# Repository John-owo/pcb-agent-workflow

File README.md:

# pcb-agent-workflow

**繁體中文** | [English](README.en.md)

用 Claude Code 或 Codex 當助手，在 KiCad 10 設計 PCB、交 JLCPCB 製造的一套工作流程。

這套流程來自一塊 4 層 GNSS 測試板（u-blox MAX-M10S，25 × 36.5 mm）從設計、審查、報價、送審、客服往返到確認生產稿的實際經驗。重複有用的做法寫成文件和 skill；踩過的雷寫成檢查項目。

**第一次做 PCB？** 從 [新手入門](docs/getting-started.md) 開始：從安裝 KiCad 走到在 JLC 下單，每一步寫你要做什麼、可以請 agent 做什麼、怎麼確認做對了。其他文件之後再看。

## 內容

| 路徑 | 內容 |
|---|---|
| [docs/getting-started.md](docs/getting-started.md) | **新手入門**：第一塊板的範圍、環境、原理圖、選料、板子規則、佈線、匯出、下單 |
| [docs/first-board-checklist.md](docs/first-board-checklist.md) | 送廠前的檢查清單，給人看，也給 agent 審查用 |
| [docs/glossary.md](docs/glossary.md) | 術語表：Gerber、BOM、CPL、DFM、工藝邊、Basic／Extended 料等 |
| [docs/workflow/collaboration.md](docs/workflow/collaboration.md) | 人與多個 agent 協作：單一寫入者、WORKLOG、接手順序、審查最多兩輪、哪些動作要使用者同意 |
| [docs/workflow/kicad-tools.md](docs/workflow/kicad-tools.md) | KiCad 原生 CLI 與 KiCad MCP 的分工、常用命令、修改 PCB 前的保全 |
| [docs/workflow/release-package.md](docs/workflow/release-package.md) | 固定發行包：內容、雜湊清單、release-checks、版本資料夾命名 |
| [docs/workflow/jlc-ordering.md](docs/workflow/jlc-ordering.md) | JLC 下單：服務等級、BOM／CPL、配料核對、壓成本、送單設定、付款後流程 |
| [skills/jlc-support/](skills/jlc-support/SKILL.md) | 跟 JLC 客服、工程、業務窗口溝通的 skill：寫信結構、六種範本、期限計算腳本、工具搭配、停止條件 |
| [skills/jlc-production-review/](skills/jlc-production-review/SKILL.md) | 審查工廠生產稿與貼裝確認的 skill：把工廠 CAM 稿對齊回原始 Gerber 逐層比對、分類差異、核對貼裝；附比對腳本與 BOM／CPL 檢查 |
| [skills/readable-schematic-layout/](skills/readable-schematic-layout/SKILL.md) | 把原理圖與佈局畫成人類好讀、好除錯的 skill：內建 symbol、電源 symbol、實際畫線、依流向分區、文字不重疊；附 netlist 比對與腳號對焊盤檢查腳本，證明只改畫法、沒改電路 |
| [skills/kicad-enclosure-step/](skills/kicad-enclosure-step/SKILL.md) | 把 KiCad 板子匯出成含全部零件的 STEP，給外殼設計用：盤點缺模型的零件、找原廠模型或依規格書自畫、對齊、用暫存副本匯出（不改板檔），逐顆自動檢查位置，最後寫外殼注意事項 |
| [.claude-plugin/marketplace.json](.claude-plugin/marketplace.json) | Claude Code 與 Codex 共用的 plugin marketplace：每個 skill 一個 plugin，加上選用的寄信確認 hook |
| [plugins/jlc-send-guard/](plugins/jlc-send-guard/) | 選用的 Claude Code hook：Gmail 寄出類工具執行前強制確認 |
| [templates/](templates/) | 新專案用的 `AGENTS.md`、`CLAUDE.md`、`WORKLOG.md`、`README.md`，以及 KiCad 專案的 `.gitignore` |
| [scripts/](scripts/) | 發行包打包驗證、Konnect stdio 呼叫器、本 repo 的隱私掃描與 skill 檢查（各 skill 專用的腳本放在 skill 自己的 `scripts/`） |
| [examples/max-m10s-breakout-revc/](examples/max-m10s-breakout-revc/README.md) | 實際下單過的範例設計包：KiCad 原生檔、Gerber、BOM、CPL、裝配圖、驗證紀錄 |
| [examples/max-m10s-breakout-revc-cad/](examples/max-m10s-breakout-revc-cad/README.md) | 上面那塊板的外殼設計用 STEP（含全部零件）、預覽圖與匯出設定；kicad-enclosure-step 的範例 |

## 流程總覽

```mermaid
flowchart LR
  A[設計<br/>KiCad 10] --> B[驗證<br/>ERC / DRC / agent 審查]
  B --> C[固定發行包<br/>雜湊清單]
  C --> D[上傳與送審<br/>配料核對]
  D --> E[付款]
  E --> F[生產稿比對]
  F --> G[使用者確認]
  G --> H[到貨與實測]
  S([jlc-support<br/>客服與工程溝通]) -.-> D
  S -.-> E
  S -.-> F
  R([jlc-production-review<br/>生產稿與貼裝審查]) -.-> F
```

## 開始使用

### 新專案

把 `templates/` 裡的四個 Markdown 檔複製到 PCB 專案根目錄，把 `<...>` 換成自己的內容；`kicad-project.gitignore` 複製後改名為 `.gitignore`。專案已經有 `README.md` 的話，不要直接覆蓋，把範本的段落合併進去。之後每次接手，agent 會從 `README.md` 和 `WORKLOG.md` 讀起。

### 安裝 skill

四個 skill 各是一個 plugin，可以只裝需要的。Claude Code 與 Codex 讀同一份 marketplace（`.claude-plugin/marketplace.json`）和同一份 `SKILL.md`。

| plugin | 用途 |
|---|---|
| `jlc-support` | 跟 JLC 客服、工程、業務窗口溝通；附確認稿期限計算 |
| `jlc-production-review` | 審查生產稿與貼裝確認；附 CAM 比對與 BOM／CPL 檢查腳本 |
| `readable-schematic-layout` | 原理圖與佈局畫成好讀、好除錯的樣子；附 netlist 與腳號對焊盤檢查 |
| `kicad-enclosure-step` | 把板子匯出成含全部零件的 STEP 給外殼設計；附盤點、匯出、逐顆位置檢查與自畫模型腳本 |
| `jlc-send-guard` | 選用的 Claude Code hook，見下方「寄信確認 hook」；預設停用 |

**Claude Code**（在對話裡輸入）：

```text
/plugin marketplace add John-owo/pcb-agent-workflow
/plugin install jlc-support@pcb-agent-workflow
```

Claude Code 2.1.275 以後也可以一步完成：`/plugin install jlc-support --marketplace John-owo/pcb-agent-workflow`。更新用 `/plugin marketplace update pcb-agent-workflow`。

**Codex**（在終端機）：

```bash
codex plugin marketplace add John-owo/pcb-agent-workflow
```

```bash
codex plugin add jlc-support@pcb-agent-workflow
```

更新用 `codex plugin marketplace upgrade`。把 `jlc-support` 換成表中其他名稱，就能裝其他 plugin。裝好後重新開一個對話，跟 agent 說「幫我寫信催 JLC 的 DFM」「幫我比對工廠寄來的生產稿」「把原理圖改成好讀的畫法，不要改電路」「我要設計外殼，給我含全部零件的 STEP」，就會套用對應的 skill。

**腳本的相依套件**：`jlc-production-review` 的 CAM 比對腳本需要 Python 3.12 與固定版本的套件，在 skill 資料夾裡執行 `python -m pip install -r scripts/requirements-cam.txt`（建議裝在 venv）。`kicad-enclosure-step` 需要 KiCad 10；它的 `step_report.py`、`simple_model.py`、`verify_placement.py` 另需 [CadQuery](https://github.com/CadQuery/cadquery)（`python -m pip install cadquery`，建議裝在 venv），範例與重現指令見 [examples/max-m10s-breakout-revc-cad](examples/max-m10s-breakout-revc-cad/README.md)。其他腳本只用 Python 標準庫。

#### 手動安裝（不用 plugin）

複製 skill 資料夾到 agent 的 skills 目錄。先建立目錄再複製；沒有這個目錄時，複製指令會把 skill 的內容直接攤在 `skills/` 底下，agent 就找不到它。

```bash
git clone https://github.com/John-owo/pcb-agent-workflow.git
```

Claude Code（macOS／Linux／Git Bash）：

```bash
mkdir -p ~/.claude/skills && cp -r pcb-agent-workflow/skills/jlc-support ~/.claude/skills/
```

Codex（Codex 文件寫的使用者 skill 目錄是 `~/.agents/skills`；舊的 `~/.codex/skills` 未驗證）：

```bash
mkdir -p ~/.agents/skills && cp -r pcb-agent-workflow/skills/jlc-support ~/.agents/skills/
```

Windows PowerShell（Codex 的話把 `.claude` 換成 `.agents`）：

```powershell
New-Item -ItemType Directory -Force "$HOME\.claude\skills" | Out-Null
Copy-Item -Recurse -Force pcb-agent-workflow\skills\jlc-support "$HOME\.claude\skills\"
```

裝好後 `~/.claude/skills/jlc-support/SKILL.md`（或 `~/.agents/skills/` 底下的同一路徑）要存在。更新時重跑同一組指令。只想在單一專案使用，就放到該專案的 `.claude/skills/` 或 `.agents/skills/`。手動安裝不含 `jlc-send-guard` hook。

#### 寄信確認 hook（選用，只限 Claude Code）

`jlc-send-guard` 在 Gmail connector 的寄出類工具（名稱含 `send`、`reply`、`forward`）執行前，強制跳出確認，auto mode 也一樣。草稿工具不受影響。它預設停用，要用時自己啟用：

```text
/plugin install jlc-send-guard@pcb-agent-workflow
/plugin enable jlc-send-guard@pcb-agent-workflow
```

限制：

- 它用正規表示式比對工具名稱：`^mcp__.*[Gg][Mm][Aa][Ii][Ll].*__.*([Ss]end|[Rr]eply|[Ff]orward)`。connector 改名後可能漏攔，請在 `/mcp` 看你的 Gmail 工具名稱有沒有被涵蓋；名稱相近的其他工具可能被多攔，多攔只會多一次確認。
- **擋不住瀏覽器上的動作。** hook 看不到頁面網址和按鈕文字，所以 Claude in Chrome 點 Confirm、Submit 不在它的範圍內；那部分只靠 skill 的硬規則和 Chrome 擴充的網站權限。
- Codex 端沒有驗證過。Codex 的 plugin hook 要先經使用者信任才會執行，ChatGPT 的 Gmail connector 能不能被攔也不確定。
- 它是多一道防線，不取代 skill 的硬規則：寄出前仍要使用者在對話中明確同意。

### 搭配的 KiCad 分析 skill

原理圖分析、BOM、DRC 審查、EMC、SPICE 等 skill 使用 [aklofas/kicad-happy](https://github.com/aklofas/kicad-happy)（MIT）。本 repo 不附副本，請依該 repo 的說明安裝。這套流程實際用到的有 `kicad`、`bom`、`jlcpcb`、`lcsc`、`datasheets`、`emc`、`spice`。

### docs/agents 是什麼

`docs/agents/` 是給 [mattpocock/skills](https://github.com/mattpocock/skills) 那套工程類 skill（`triage`、`to-tickets`、`to-spec` 等）讀的設定：issue 記在哪裡、triage 標籤叫什麼。沒安裝那套 skill 就用不到，可以忽略。

### Codex 與 Claude Code 交接

兩個 agent 輪流接手同一個任務時，交接格式見 [John-owo/codex-cc-handoff](https://github.com/John-owo/codex-cc-handoff)。

## 核心原則

- **一個工作目錄同時只有一位寫入者。** 換手時在 WORKLOG 記錄 owner 與停止點。
- **改 PCB 前先保全完整備份。** 雜湊清單只能識別檔案，不能還原。
- **ERC／DRC 通過，不等於電氣正確、板廠接受或實板能動。**
- **付款、送單、寄信、確認生產稿，每一次都等使用者同意。** agent 做到起草和準備為止。唯一的例外是催辦與純技術澄清：使用者可以說明範圍和期限，事先授權。
- **固定發行包與動態進度分開。** 交給工廠的版本不再改；訂單進度另外記。

## 限制

- 範例板完成了 ERC／DRC 與 agent 審查，並由 JLCPCB 製造與 SMT 組裝。兩片組裝板已完成實測：上電、UART、被動天線 3D 定位、PPS 1 Hz 與 I2C 皆通過；回灌 A-GNSS 輔助資料後，定位時間約縮短為冷啟動的 1/8。範例是送單時的發行包；工廠 CAM 之後做的微調不在裡面。實測程序與結果見 [examples/max-m10s-breakout-revc-tests](examples/max-m10s-breakout-revc-tests/README.md)。
- JLC 的期限、價格、料庫狀態是 2026-09 的觀察，以當下的網站和信件為準。
- 流程以 Windows、KiCad 10、JLCPCB 為主要環境。其他板廠可以參考溝通原則，但網站流程不同。

## 支援範圍

這套流程只在下面的環境驗證過：

| 項目 | 支援 |
|---|---|
| 作業系統 | Windows |
| EDA | KiCad 10 |
| agent | Claude Code、Codex（兩者都要能用）。plugin 安裝在 Claude Code 2.1.299、Codex CLI 0.163 測過 |
| 板廠 | JLCPCB |
| 收貨地 | 台灣（順豐） |

SKILL.md 與腳本是兩個 agent 共用的基準。只有 Claude Code 驗證過的加強功能另外標明：目前只有 `jlc-send-guard` hook。拿掉它，skill 一樣完整，硬規則照樣適用。

其他環境（macOS、Linux、其他 KiCad 版本、PCBWay 等其他板廠）可能可以用，但沒有驗證。這類 issue 會標成 `wontfix`，回覆「可能可用，未驗證」；溝通原則不受板廠限制，可以照用。

## 授權

MIT，見 [LICENSE](LICENSE)。範例中改自 KiCad 官方元件庫的 footprint 與 symbol，以及其他第三方內容的來源，見 [NOTICE](NOTICE)。原廠 datasheet 不隨附，範例 README 列有原廠連結。

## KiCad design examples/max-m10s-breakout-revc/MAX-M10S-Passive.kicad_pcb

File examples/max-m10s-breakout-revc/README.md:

# MAX-M10S 被動天線 GNSS 轉接板（Rev C，OSP，僅頂面組裝）

以 u-blox MAX-M10S 為核心的小型 GNSS 轉接板，接被動式天線，供麵包板或主控板以 UART／I2C 使用。原生設計為 KiCad 10，發行日期 2026-09-21。

## 板子規格

- 尺寸 25.0 × 36.5 mm，4 層，板厚 1.6 mm，表面處理 OSP，疊構按 JLC04161H-7628 設定。
- U1：MAX-M10S-00B，使用預設低增益內建 LNA。
- J1：I-PEX MHF I（20279-001E-03）接被動式 50 Ω 天線，不供天線電源。D1 為天線端 ESD 保護。
- J2、J3：兩支 1×6、2.54 mm 排針，從板底插入，兩排間距 17.78 mm。
- TX／RX／PPS 串 33 Ω，I2C 有 4.7 kΩ 上拉，電源 LED，PPS LED 經 BSS138 緩衝。另有 5 個測試焊盤（TP1、TP2、TP4–TP6）。
- 無 RTC 備援電源：U1 pin 6（V_BCKP）刻意不接，板上沒有電池或超級電容。
- 原理圖註記：UART 9600 8N1，I2C 位址 0x42。

## 接線

- 只接外部穩壓 3.3 V 電源與 3.3 V 邏輯，不耐 5 V。
- 模組 TX → 主控 RX，模組 RX → 主控 TX，並共地。
- 排針由天線端往下：
  - J2：3V3 / GND / TX / RX / PPS / EXTINT
  - J3：GND / SCL / SDA / RESET_N / SAFEBOOT_N / GND
- 沒有備援電源，完全斷電後需由主控重新設定 GNSS。
- 移除 GNSS 電源前先斷開主控訊號。
- PPS LED 閃爍不代表已定位。

## 檔案

| 路徑 | 內容 |
|---|---|
| `MAX-M10S-Passive.kicad_pro` / `.kicad_sch` / `.kicad_pcb` / `.kicad_dru` | KiCad 10 原生專案、原理圖、PCB、自訂設計規則 |
| `fp-lib-table`、`sym-lib-table` | 專案元件庫表，以 `${KIPRJMOD}` 相對路徑指向下兩項 |
| `footprints/PassiveGNSS.pretty/` | 專案 footprint 庫 |
| `symbols/PassiveGNSS.kicad_sym` | 專案 symbol 庫 |
| `design.json` | 元件、網路、料號與 PCB 座標的機器可讀摘要（KiCad 不讀此檔） |
| `manufacturing/gerbers-board.zip` | 單板 Gerber、鑽孔檔與 Gerber job 檔 |
| `manufacturing/BOM-JLCPCB-top-only.csv` | 板廠組裝 BOM：11 組料、每片 17 個元件，含 LCSC 料號 |
| `manufacturing/CPL-board-top-only.csv` | 板廠貼片座標，僅 Top，單板座標 |
| `manufacturing/assembly-orientation.pdf` / `.csv` / `-1.png` | 裝配方向圖與對照表（pin 1、極性端、座標） |
| `manufacturing/BOM-customer-headers.csv` | 自行焊接的排針 J2、J3 |
| `manufacturing/schematic.pdf` | 原理圖 PDF |
| `verification/erc.json`、`drc.json` | 發行時的原生 ERC／DRC 結果 |
| `verification/release-checks.json` | 發行差異核對摘要 |
| `verification/independent-release-review.md` | 獨立審查紀錄（範圍見下文） |

`PassiveGNSS` 庫裡還有 Rev C 板上沒用到的項目：footprint `ADCM_S05R5SA`、`CPH3225A`（已移除的備援電源）、`Fiducial_1mm`、`ToolingHole_2mm`，symbol `BAS116`、`C_Polarized`、`D`。部分 footprint／symbol 衍生自 KiCad 官方元件庫，來源與授權見 repo 的 NOTICE。

## 製造用哪些檔

以下四項是同一套，一起使用，不要和其他版本的檔案混用：

1. `manufacturing/gerbers-board.zip`：製板
2. `manufacturing/BOM-JLCPCB-top-only.csv`：組裝 BOM
3. `manufacturing/CPL-board-top-only.csv`：貼片座標
4. `manufacturing/assembly-orientation.pdf`（另有 `.csv`、`.png`）：裝配方向，用來核對板廠的貼片預覽

補充：

- Gerber 是單板，不含拼板工藝邊和定位點。原發行時的安排是由板廠加工藝邊與定位點、交貨前拆邊；這項服務與做法須由板廠確認。
- 工廠只組裝頂面 17 個元件。J2、J3 排針不在組裝 BOM／CPL 內，依 `BOM-customer-headers.csv` 自行從板底插入焊接（每片 2 支）。原生設計仍保留 J2、J3，作為成品的一部分。
- OSP 板收到後盡早焊排針。

## 已驗證

- **原生 ERC／DRC**（KiCad 10.0.6，發行時 2026-09-21）：ERC 0 項違規；DRC 0 項違規、0 個未連線項目、0 個原理圖／PCB 一致性問題。報告含 error、warning、exclusion 三種等級，見 `verification/`。
- **本副本重跑**（2026-10-02，KiCad 10.0.6 `kicad-cli`，`--severity-all`，DRC 加 `--schematic-parity`）：結果相同。元件庫經 `${KIPRJMOD}` 正常載入，沒有缺 symbol 或 footprint 的警告。這次重跑的輸出沒有放進套件，以免改動發行時的 `verification/`；可以用 [kicad-tools.md](../../docs/workflow/kicad-tools.md) 第 5 節的命令自行重現。
- **發行差異核對**（`release-checks.json`）：與前一版 Rev C 相比，PCB 幾何、走線、焊盤與網路不變。這一版只改了 D1 料號文字、資料表連結、OSP 製造屬性與組裝清單。Gerber ZIP 與當時上傳板廠的檔案逐位元相同。
- **獨立審查**（`independent-release-review.md`）：由唯讀的審查 agent 檢查發行檔案（README、BOM、CPL、裝配表、ERC／DRC 報告等）彼此是否一致，沒有發現致命的不一致或遺漏。審查範圍只到這些檔案的一致性；審查的是原始發行版的 README，本 README 為公開範例重寫，不在審查範圍內。審查者沒有重新開啟或重算 Gerber ZIP，也沒有核對網站狀態、疊構實作、PDF 呈現、電氣／RF／EMC／DFM 行為或實板。

## 未驗證

- ERC／DRC 通過，不代表電路正確、板廠會接受，或實板能正常工作。
- EMC：先前的設計審查只做過 EMC 啟發式分析，留下未經實測的風險提示，例如介面訊號換層處 1 mm 內沒有獨立的 GND stitching via。這些不算通過 EMC，也沒有做過 EMC 測試。
- SPICE：自動模擬因本機模擬器逾時而跳過，沒有 SPICE 通過的結果。
- 這一版只核對交付差異，不是重新做的完整電氣／EMC 驗證。
- 板廠 DFM 審核與貼片確認的結果不在本套件內。板廠的最終生產稿與元件方向須另行確認。
- 兩片組裝板已通過實測程序第 3–7 步；M10S 輔助定位只在實板試過一次回灌（MGA-DBD＋位置）。實測程序與結果見 [max-m10s-breakout-revc-tests](../max-m10s-breakout-revc-tests/README.md)。先前在 NEO-6M 上做的 ALP／AOP 測試，不能當作 M10S 的結果。

## 已知注意事項

- **D1 footprint 名稱與實際料號不同**：footprint 名稱是 `PassiveGNSS:PESD3V3C1BSF`，實際料號是 Nexperia PESD3V3Z1BSFYL（LCSC C2908830）。兩者用同一組焊盤（DSN0603-2／SOD962-2，0.4 mm pitch），footprint 名稱沒改。採購以 BOM 的料號為準。
- **D1 焊盤間距**：依 Nexperia 建議焊盤，兩焊盤實際間距約 0.144 mm，小於專案預設間距（網路類別 0.2 mm）。`.kicad_dru` 對 D1 焊盤之間（0.13 mm）以及 RF 走線到 D1 焊盤（0.15 mm）設了局部規則，另規定 RF 與 GND 鋪銅保持 1.0 mm。
- **Gerber job 檔的表面處理欄位**：`gerbers-board.zip` 內 `MAX-M10S-Passive-job.gbrjob` 的 `Finish` 寫的是 `ENIG`，而 PCB 設定與本版製造規格都是 OSP。Gerber 沒有在改成 OSP 後重新產生，所以下單時要在訂單上選 OSP。
- **J1 座標**：CPL 用的是連接器的機構中心 (15.800, 33.700)，和 RF 接點焊盤 (15.800, 32.175) 位置不同。須確認外殼和中心接點的方向。
- **極性**：元件頂面的標記不一定代表極性。D2、D3、Q1、U1 都要依 `assembly-orientation.pdf` 的 pin 1 和極性端，比對板廠的貼片預覽。
- **design.json 的元件數**：備註寫 19 個元件，這個數字包含自行焊接的 J2、J3；板廠組裝是 17 個。
- 設計時曾和 SparkFun 公開的 MAX-M10S breakout 原理圖逐項比較差異與取捨。本設計的電路與檔案是重新繪製的，沒有複製 SparkFun 的檔案。
- U1 與 J1 的 footprint 依原廠資料建立：MAX-M10S Integration Manual UBX-20053088 R05（焊盤、鋼網開口），I-PEX 20279 圖面 rev.29。這些原廠資料沒有附在本套件內。

## 原廠資料表

原廠資料表、整合手冊和圖面有著作權，不附在本套件內，請到原廠網站下載。下表取自原理圖 symbol 的 Datasheet 欄位：

| 位號 | 料號 | 廠商 | 資料表 |
|---|---|---|---|
| U1 | MAX-M10S-00B | u-blox | https://content.u-blox.com/sites/default/files/MAX-M10S_DataSheet_UBX-20035208.pdf |
| D1 | PESD3V3Z1BSFYL | Nexperia | https://assets.nexperia.com/documents/data-sheet/PESD3V3Z1BSF.pdf |
| Q1 | BSS138 | onsemi | https://www.onsemi.com/pdf/datasheet/bss138-d.pdf |

其他元件（電阻、電容、LED、J1、排針）的 Datasheet 欄位是空的，可依 BOM 上的製造商料號到原廠網站查詢。

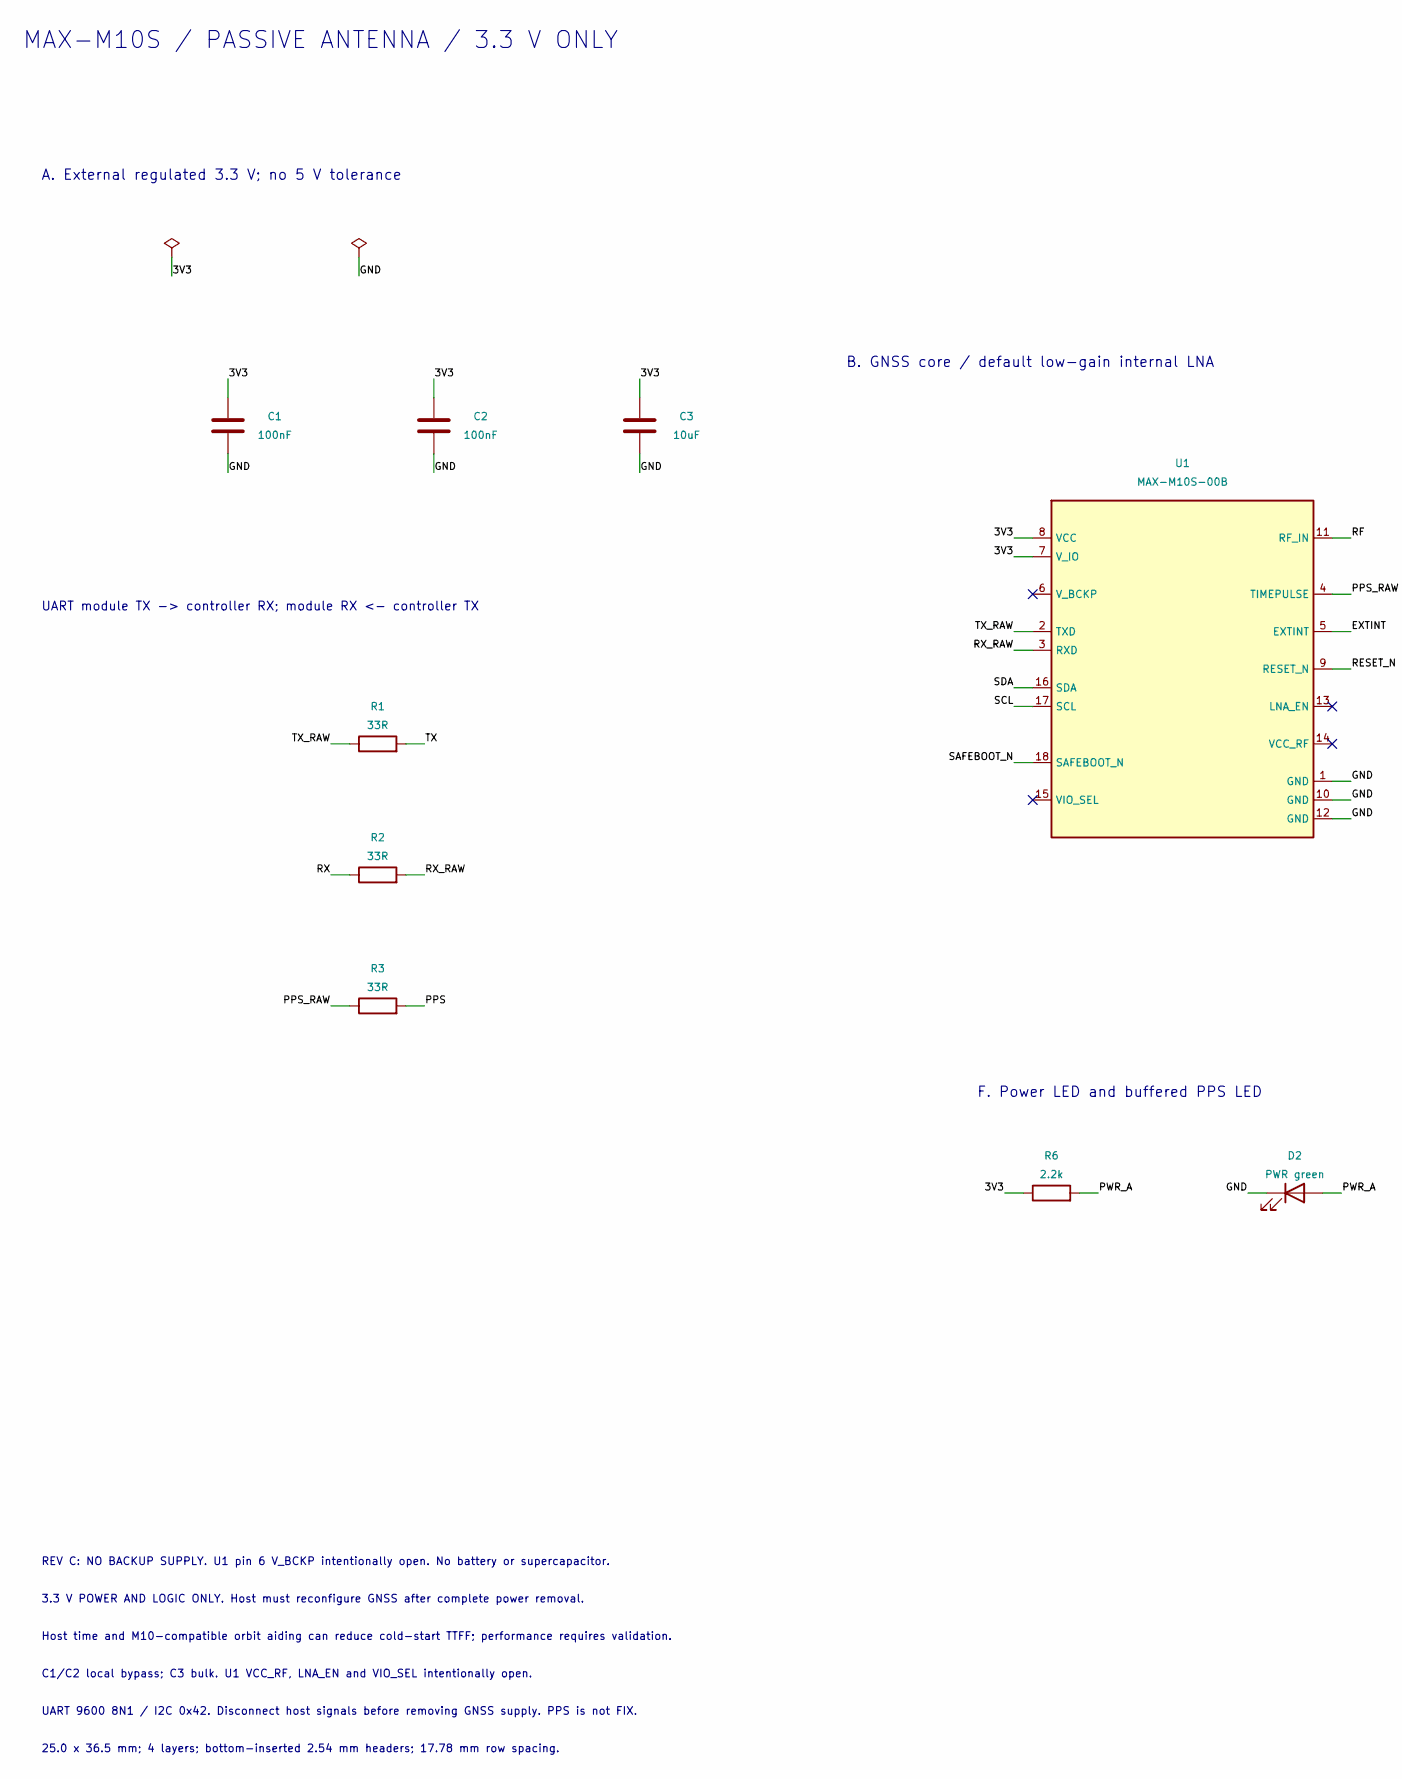
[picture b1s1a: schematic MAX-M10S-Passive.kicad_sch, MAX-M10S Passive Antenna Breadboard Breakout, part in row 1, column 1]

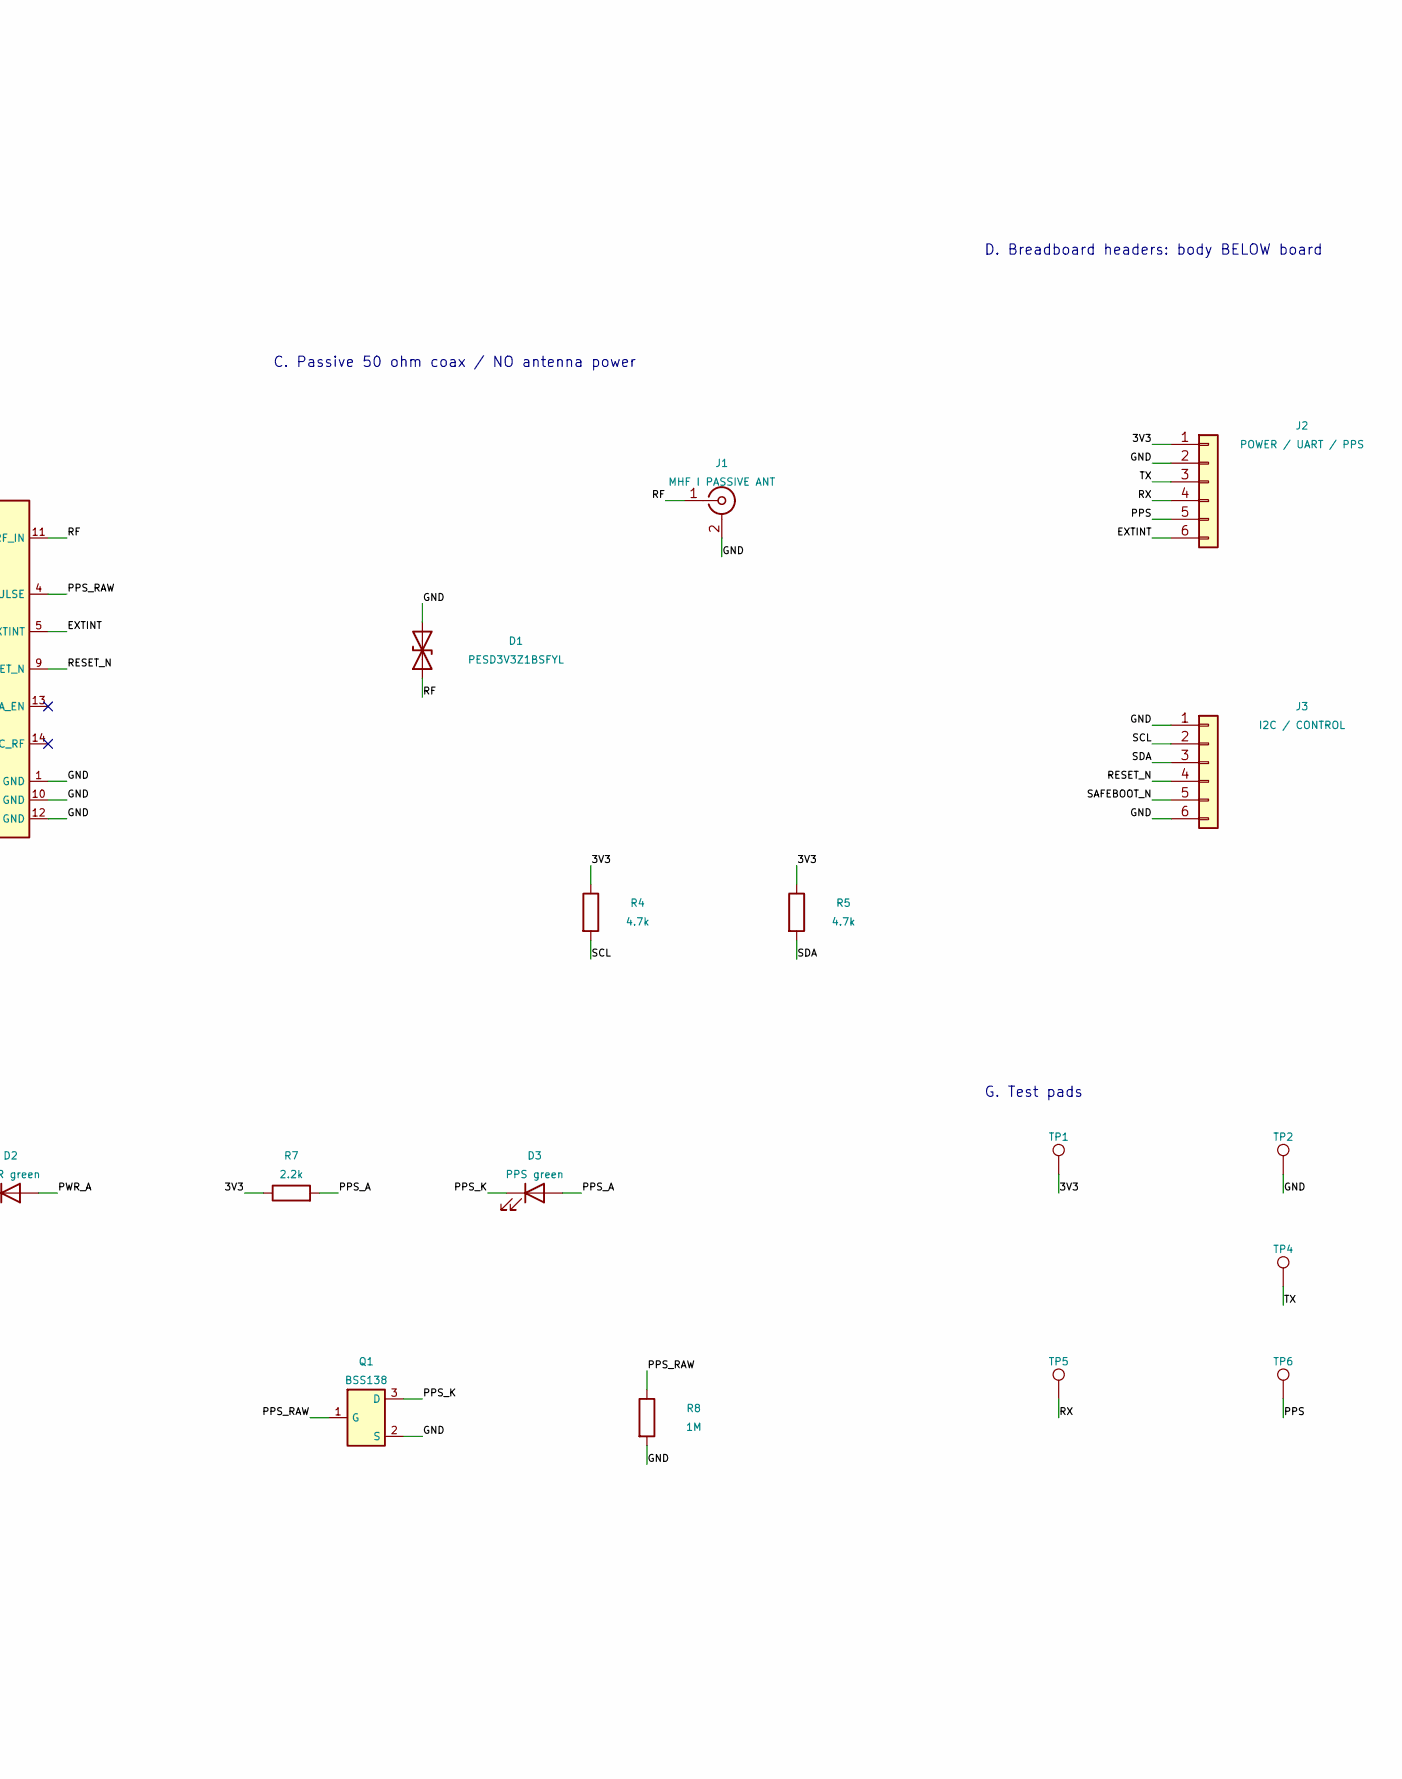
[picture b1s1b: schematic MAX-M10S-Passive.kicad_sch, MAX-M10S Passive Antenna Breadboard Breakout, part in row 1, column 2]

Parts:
C1, C2: 100nF; C_0603; MPN CC0603KRX7R9BB104; LCSC Part Number C14663
C3: 10uF; C_0603; MPN CL10A106KP8NNNC; LCSC Part Number C19702
D1: PESD3V3Z1BSFYL; PESD3V3C1BSF; MPN PESD3V3Z1BSFYL; LCSC Part Number C2908830
D2: PWR green; LED_0603; MPN 19-21/G6C-FM1N2B/4T; LCSC Part Number C2984263
D3: PPS green; LED_0603; MPN 19-21/G6C-FM1N2B/4T; LCSC Part Number C2984263
J1: MHF I PASSIVE ANT; MHF_I; MPN 20279-001E-03; LCSC Part Number C3173448
J2: POWER / UART / PPS; Header_1x06; MPN HX PH254-01-06-Z-L11.5; LCSC Part Number C52016393
J3: I2C / CONTROL; Header_1x06; MPN HX PH254-01-06-Z-L11.5; LCSC Part Number C52016393
Q1: BSS138; SOT23; MPN BSS138; LCSC Part Number C52895
R1, R2, R3: 33R; R_0603; MPN 0603WAF330JT5E; LCSC Part Number C23140
R4, R5: 4.7k; R_0603; MPN 0603WAF4701T5E; LCSC Part Number C23162
R6, R7: 2.2k; R_0603; MPN 0603WAF2201T5E; LCSC Part Number C4190
R8: 1M; R_0603; MPN 0603WAF1004T5E; LCSC Part Number C22935
TP1: 3V3; TestPoint; MPN PCB feature
TP2: GND; TestPoint; MPN PCB feature
TP4: TX; TestPoint; MPN PCB feature
TP5: RX; TestPoint; MPN PCB feature
TP6: PPS; TestPoint; MPN PCB feature
U1: MAX-M10S-00B; MAX_M10S; MPN MAX-M10S-00B; LCSC Part Number C4153167

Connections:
/3V3: C1.1, C2.1, C3.1, J2.1, R4.1, R5.1, R6.1, R7.1, TP1.1, U1.7 (V_IO), U1.8 (VCC)
/EXTINT: J2.6, U1.5 (EXTINT)
/GND: C1.2, C2.2, C3.2, D1.2 (A2), D2.1 (K), J1.2 (Ext), J2.2, J3.1, J3.6, Q1.2 (S), R8.2, TP2.1, U1.1 (GND), U1.10 (GND), U1.12 (GND)
/PPS: J2.5, R3.2, TP6.1
/PPS_A: D3.2 (A), R7.2
/PPS_K: D3.1 (K), Q1.3 (D)
/PPS_RAW: Q1.1 (G), R3.1, R8.1, U1.4 (TIMEPULSE)
/PWR_A: D2.2 (A), R6.2
/RESET_N: J3.4, U1.9 (RESET_N)
/RF: D1.1 (A1), J1.1 (In), U1.11 (RF_IN)
/RX: J2.4, R2.1, TP5.1
/RX_RAW: R2.2, U1.3 (RXD)
/SAFEBOOT_N: J3.5, U1.18 (SAFEBOOT_N)
/SCL: J3.2, R4.2, U1.17 (SCL)
/SDA: J3.3, R5.2, U1.16 (SDA)
/TX: J2.3, R1.2, TP4.1
/TX_RAW: R1.1, U1.2 (TXD)

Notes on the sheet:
MAX-M10S / PASSIVE ANTENNA / 3.3 V ONLY
A. External regulated 3.3 V; no 5 V tolerance
B. GNSS core / default low-gain internal LNA
C. Passive 50 ohm coax / NO antenna power
D. Breadboard headers: body BELOW board
UART module TX -> controller RX; module RX <- controller TX
F. Power LED and buffered PPS LED
G. Test pads
REV C: NO BACKUP SUPPLY. U1 pin 6 V_BCKP intentionally open. No battery or supercapacitor.
3.3 V POWER AND LOGIC ONLY. Host must reconfigure GNSS after complete power removal.
Host time and M10-compatible orbit aiding can reduce cold-start TTFF; performance requires validation.
C1/C2 local bypass; C3 bulk. U1 VCC_RF, LNA_EN and VIO_SEL intentionally open.
UART 9600 8N1 / I2C 0x42. Disconnect host signals before removing GNSS supply. PPS is not FIX.
25.0 x 36.5 mm; 4 layers; bottom-inserted 2.54 mm headers; 17.78 mm row spacing.

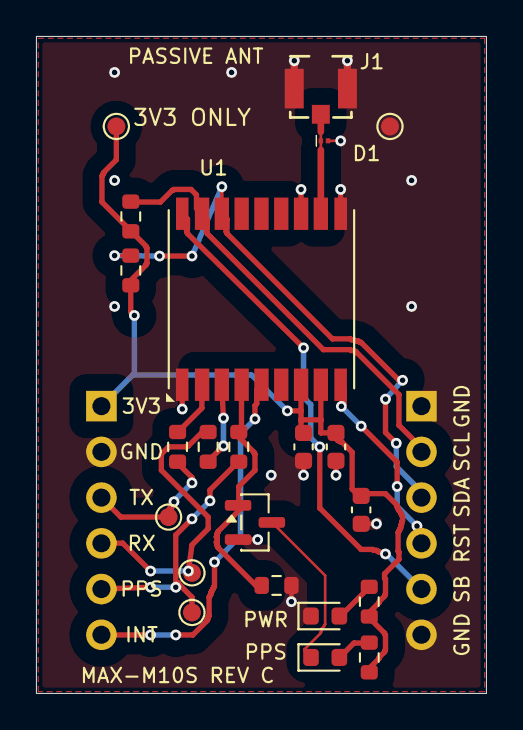
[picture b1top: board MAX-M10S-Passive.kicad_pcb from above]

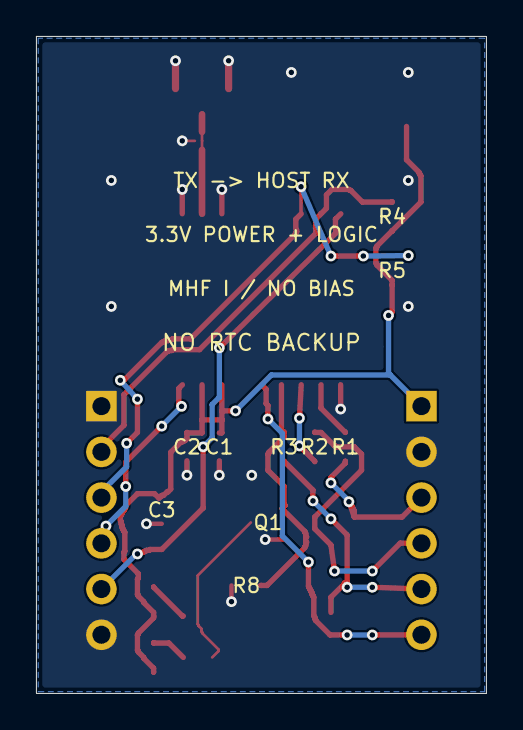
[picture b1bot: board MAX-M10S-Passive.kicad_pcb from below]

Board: 4 copper layers, 25.0 x 36.5 mm, 24 parts (2 on the bottom side), 17 nets.
